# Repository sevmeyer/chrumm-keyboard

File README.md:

Chrumm keyboard
===============

Chrumm is an open-hardware ergonomic keyboard,
made of a 3D-printable body, a bendable PCB,
and custom firmware for the Raspberry Pi Pico.

This repository contains all relevant source files.
I share these files in the hope that they are useful, or
at least interesting to others. Keep in mind that this is
a free, do-it-yourself project. What you see is what you get.
Make sure to check the license.

Files
-----

- [Releases] - Download page for STL, 3MF, GBR, UF2 files
- [BUILD.md](BUILD.md) - Build advice
- [MATERIALS.md](MATERIALS.md) - Bill Of Materials
- [pcb/README.md](pcb/README.md) - PCB production details
- [body/README.md](body/README.md) - Body generator parameters
- [firmware/README.md](firmware/README.md) - Firmware overview and installation

[Releases]: https://github.com/sevmeyer/chrumm-keyboard/releases/

Features
--------

Chrumm features a column staggered layout with simple thumb clusters.
The right side has an additional column, to better approximate
the standard ANSI layout, and to provide dedicated arrow keys.
A central encoder allows for rotational input.

The body is a robust monoblock without visible screws. It has
integrated split, tent, and tilt angles, similar to commercial
ergonomic boards. The palm rests and the USB cable are firmly
attached, so that everything can be moved around without hassle.

The STL files are generated programmatically, with a pure
Python package that has no dependencies. They are optimized
for FFF 3D printing. Most parts are printed sideways, to
produce a smooth surface without the need of post-processing.
Custom supports minimize the print time and filament cost.

The body houses two reversible, bendable, interconnected PCBs.
They are powered by a Raspberry Pi Pico.

Layout
------

Credit
------

Chrumm would not exist without the shared knowledge of the
mechanical keyboard community.

I found inspiration on [Reddit], [KBD.news], [geekhack], and
learned a lot from the [PCB guides] by ai03 and Ruiqi Mao, the
[Keyboard posts] by Masterzen, and the [Matrix Help] by Dave Dribin.

The layout and body is influenced by projects like the [Ergodox],
[Dactyl], [Sofle], [Pteron], and everything from [Bastardkb].
I also used established open hardware repositories for reference,
including the [UHK60], [Skeletyl], [Sofle], [Corne], and [Torn].

[Reddit]: https://old.reddit.com/r/ErgoMechKeyboards+MechanicalKeyboards/
[KBD.news]: https://kbd.news/
[geekhack]: https://geekhack.org
[PCB guides]: https://wiki.ai03.com/books/pcb-design
[Keyboard posts]: https://www.masterzen.fr/tag/#mechanical-keyboards
[Matrix Help]: https://www.dribin.org/dave/keyboard/one_html/
[Ergodox]: https://www.ergodox.io/
[Dactyl]: https://github.com/adereth/dactyl-keyboard
[Sofle]: https://github.com/josefadamcik/SofleKeyboard
[Pteron]: https://github.com/FSund/pteron-keyboard
[Bastardkb]: https://bastardkb.com/
[UHK60]: https://github.com/UltimateHackingKeyboard/uhk60v1-electronics
[Skeletyl]: https://github.com/Bastardkb/Skeletyl-PCB-plate
[Corne]: https://github.com/foostan/crkbd
[Torn]: https://github.com/rtitmuss/torn

Gallery
-------

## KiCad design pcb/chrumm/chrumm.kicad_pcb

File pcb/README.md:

Chrumm PCB
==========

The PCB is made with [KiCad], version 7.

The PCB is reversible. It covers half of the keyboard,
and is flipped over for the other half. It is intended
to slightly bend between the pinky and ring finger,
therefore the board thickness should not exceed 0.8mm.

All connections are through-hole (or castelated), so
that they can be soldered with basic hobby equipment.
The switch pin holes are implemented as slots, to
provide a snug fit for the flat pins, and thus
minimize the required amount of solder.

[KiCad]: https://www.kicad.org/

Teardrops
---------

The teardrops are generated with a custom [KiCad plugin],
using the following settings:

    PTH arc radius: 250%
    SMD arc radius: 250%
    Via arc radius: 350%

[KiCad plugin]: https://github.com/sevmeyer/kicad-arc-teardrops

Production
----------

I ordered the prototypes from [PCBWay] (no affiliation).
Other manufacturers are available, check for example
[PCBShopper] or [Manufacturing Reports]. Here are some of
the relevant specifications, use them at your own discretion:

- Standard PCB (not flex)
- Single pieces (not panelized)
- Layers: 2
- Material: FR4 TG 150-160
- Thickness: 0.8mm (at most)
- Surface finish: HASL (lead free)
- Copper thickness: 1oz

[PCBWay]: https://pcbway.com/
[PCBShopper]: https://pcbshopper.com/
[Manufacturing Reports]: https://manufacturingreports.com/category/electronics/rigid-pcb-fabrication/

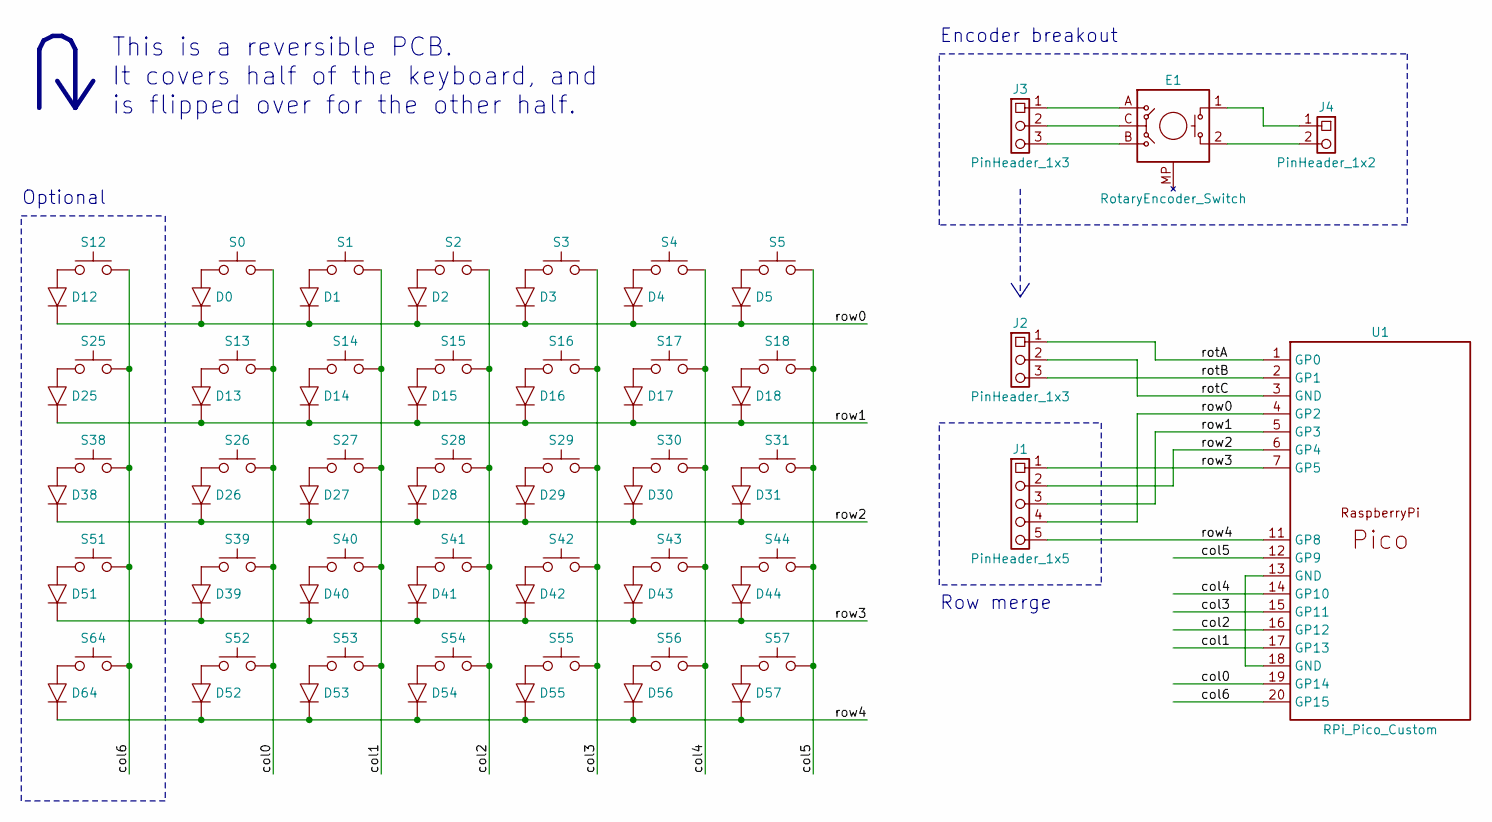
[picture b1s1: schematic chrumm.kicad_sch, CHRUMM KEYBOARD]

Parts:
D0, D1, D2, D3, D4, D5, D12, D13, D14, D15, D16, D17, D18, D25, D26, D27, D28, D29, D30, D31, D38, D39, D40, D41, D42, D43, D44, D51, D52, D53, D54, D55, D56, D57, D64: Diode
E1: RotaryEncoder_Switch
J1: PinHeader_1x5
J2, J3: PinHeader_1x3
J4: PinHeader_1x2
S0, S1, S2, S3, S4, S5, S12, S13, S14, S15, S16, S17, S18, S25, S26, S27, S28, S29, S30, S31, S38, S39, S40, S41, S42, S43, S44, S51, S52, S53, S54, S55, S56, S57, S64: Switch
U1: RPi_Pico_Custom

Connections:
/col0: S0.1, S13.1, S26.1, S39.1, S52.1, U1.19 (GP14)
/col1: S1.1, S14.1, S27.1, S40.1, S53.1, U1.17 (GP13)
/col2: S2.1, S15.1, S28.1, S41.1, S54.1, U1.16 (GP12)
/col3: S3.1, S16.1, S29.1, S42.1, S55.1, U1.15 (GP11)
/col4: S4.1, S17.1, S30.1, S43.1, S56.1, U1.14 (GP10)
/col5: S5.1, S18.1, S31.1, S44.1, S57.1, U1.12 (GP9)
/col6: S12.1, S25.1, S38.1, S51.1, S64.1, U1.20 (GP15)
/rotA: J2.1, U1.1 (GP0)
/rotB: J2.3, U1.2 (GP1)
/rotC: J2.2, U1.3 (GND)
/row0: D0.1 (K), D1.1 (K), D2.1 (K), D3.1 (K), D4.1 (K), D5.1 (K), D12.1 (K), J1.4, U1.4 (GP2)
/row1: D13.1 (K), D14.1 (K), D15.1 (K), D16.1 (K), D17.1 (K), D18.1 (K), D25.1 (K), J1.3, U1.5 (GP3)
/row2: D26.1 (K), D27.1 (K), D28.1 (K), D29.1 (K), D30.1 (K), D31.1 (K), D38.1 (K), J1.2, U1.6 (GP4)
/row3: D39.1 (K), D40.1 (K), D41.1 (K), D42.1 (K), D43.1 (K), D44.1 (K), D51.1 (K), J1.1, U1.7 (GP5)
/row4: D52.1 (K), D53.1 (K), D54.1 (K), D55.1 (K), D56.1 (K), D57.1 (K), D64.1 (K), J1.5, U1.11 (GP8)
unnamed: D0.2 (A), S0.2
unnamed: D1.2 (A), S1.2
unnamed: D2.2 (A), S2.2
unnamed: D3.2 (A), S3.2
unnamed: D4.2 (A), S4.2
unnamed: D5.2 (A), S5.2
unnamed: D12.2 (A), S12.2
unnamed: D13.2 (A), S13.2
unnamed: D14.2 (A), S14.2
unnamed: D15.2 (A), S15.2
unnamed: D16.2 (A), S16.2
unnamed: D17.2 (A), S17.2
unnamed: D18.2 (A), S18.2
unnamed: D25.2 (A), S25.2
unnamed: D26.2 (A), S26.2
unnamed: D27.2 (A), S27.2
unnamed: D28.2 (A), S28.2
unnamed: D29.2 (A), S29.2
unnamed: D30.2 (A), S30.2
unnamed: D31.2 (A), S31.2
unnamed: D38.2 (A), S38.2
unnamed: D39.2 (A), S39.2
unnamed: D40.2 (A), S40.2
unnamed: D41.2 (A), S41.2
unnamed: D42.2 (A), S42.2
unnamed: D43.2 (A), S43.2
unnamed: D44.2 (A), S44.2
unnamed: D51.2 (A), S51.2
unnamed: D52.2 (A), S52.2
unnamed: D53.2 (A), S53.2
unnamed: D54.2 (A), S54.2
unnamed: D55.2 (A), S55.2
unnamed: D56.2 (A), S56.2
unnamed: D57.2 (A), S57.2
unnamed: D64.2 (A), S64.2
unnamed: E1.1, J4.1
unnamed: E1.2, J4.2
unnamed: E1.A, J3.1
unnamed: E1.B, J3.3
unnamed: E1.C, J3.2
unnamed: U1.13 (GND), U1.18 (GND)

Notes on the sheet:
Encoder breakout
Optional
Row merge
This is a reversible PCB. It covers half of the keyboard, and is flipped over for the other half.

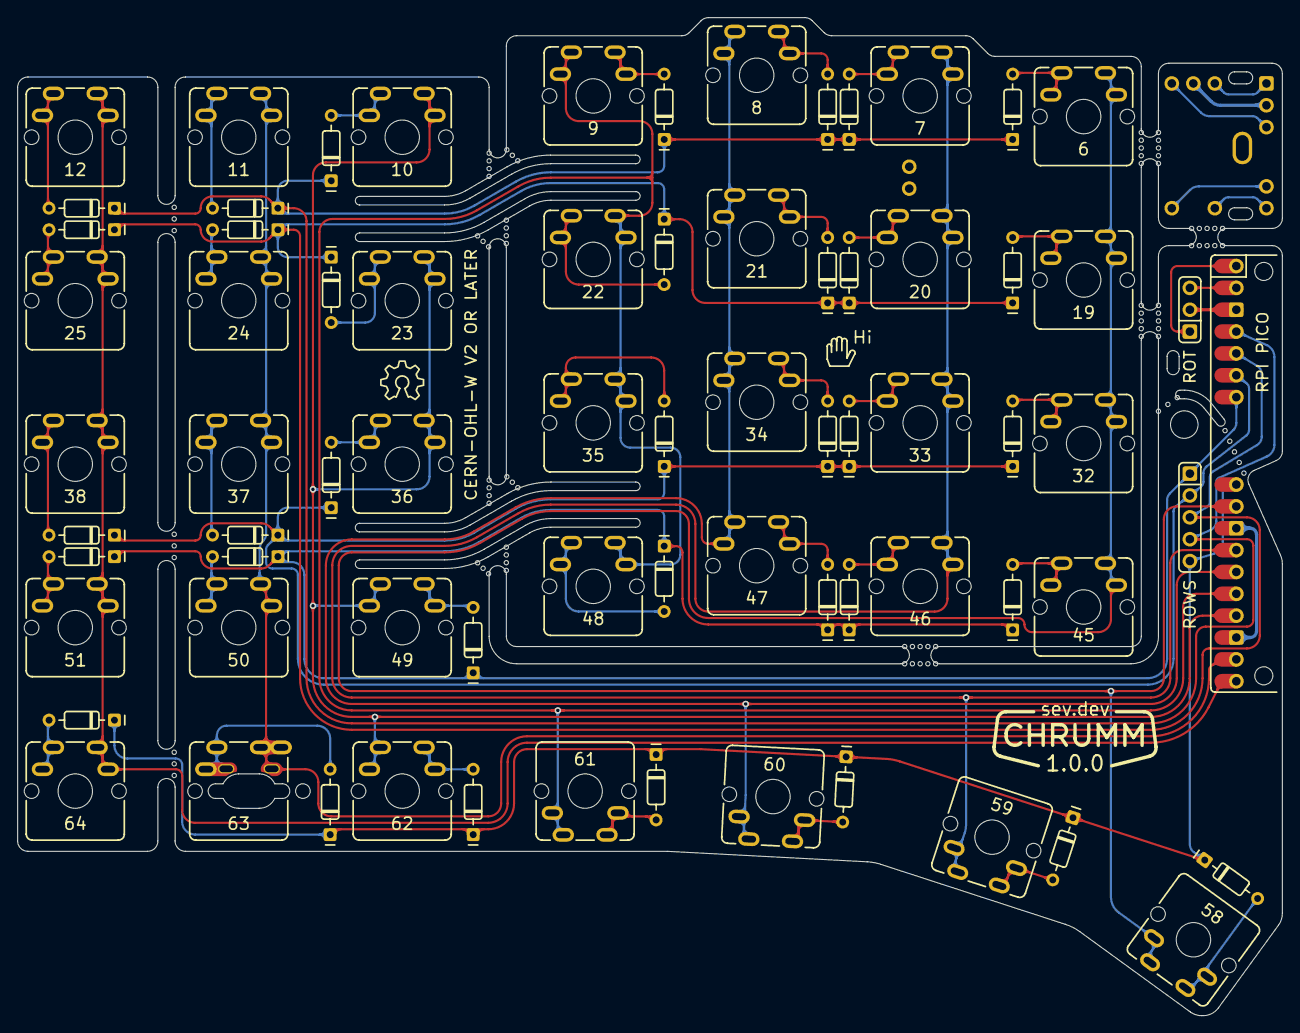
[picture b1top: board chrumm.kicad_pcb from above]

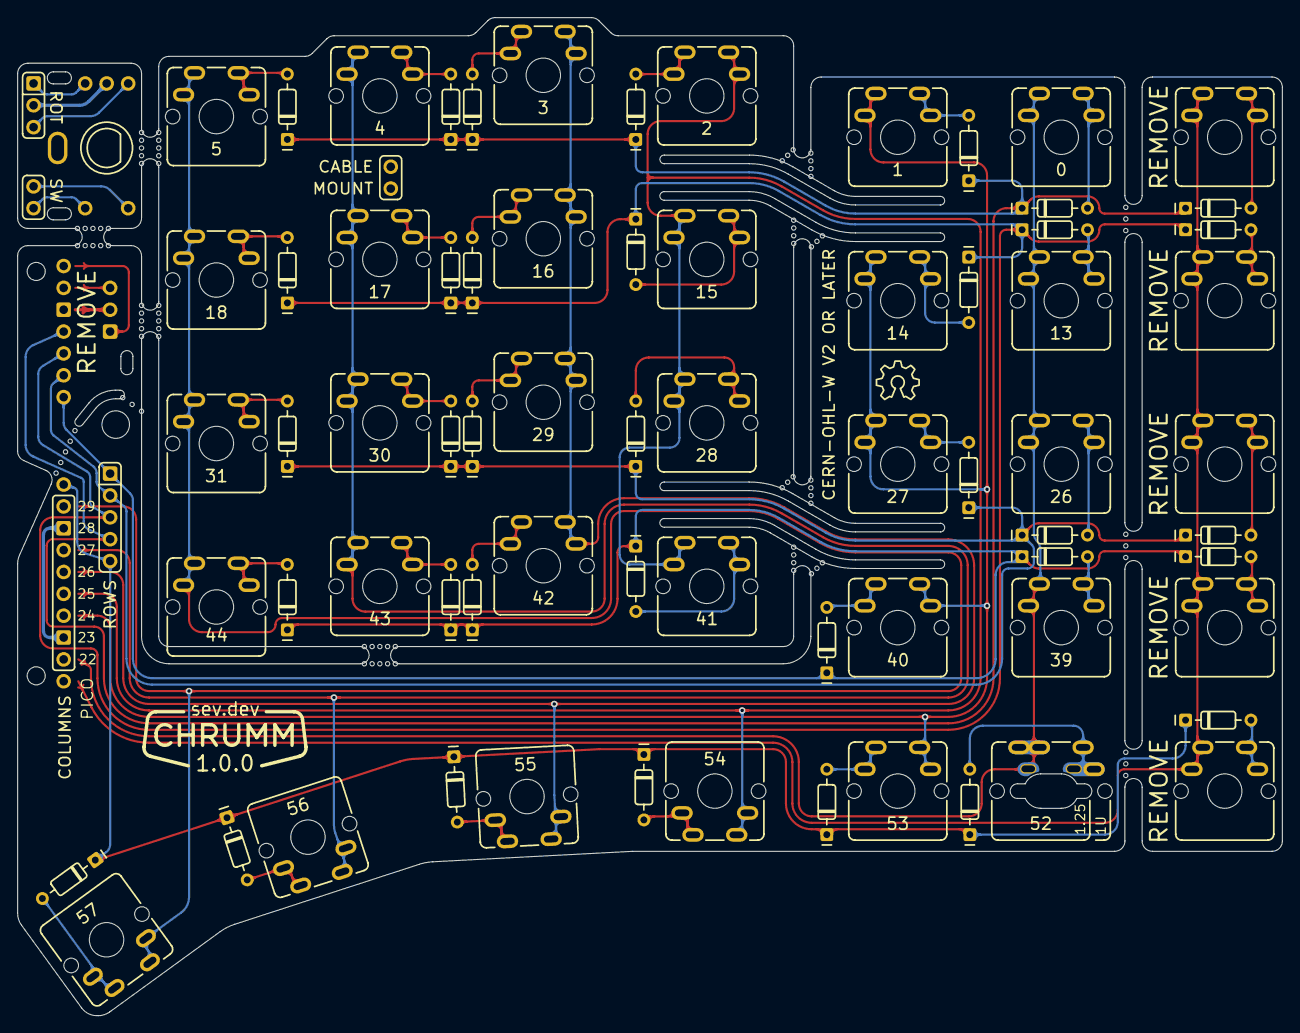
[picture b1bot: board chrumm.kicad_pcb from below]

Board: 2 copper layers, 147.0 x 116.0 mm, 76 parts (9 on the bottom side), 56 nets.

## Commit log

2020-07-03 Fix spelling
2020-08-13 Write each slice to separate file
2020-10-13 Update doc
2020-12-30 Update build log link
2022-09-17 Revise color in doc images
2023-10-04 Release version 1.0
2023-10-06 Add small clarifications to README
2023-10-08 Add keycap set name and diode advice to README
2023-10-09 Add layer count to PCB order details
2023-10-19 Add link to QMK config
2023-10-19 Add kBOOT keycode to trigger bootloader mode
2023-10-19 Remove cRWND and cFFWD from default layout
2023-11-07 Revise matrix comments in firmware
2023-11-07 Revise pin settle time and encoder keypress ticks
2023-11-07 Release firmware 1.0.1
2023-11-22 Revise matrix doc comments
2023-11-22 Use PID 1209:5E7C as registered on pid.codes
2023-12-03 Release firmware 1.0.2
2023-12-03 Revise Face triangulation for better performance
2023-12-03 Remove obsolete draft.json
2023-12-03 Revise body generator comments
2023-12-03 Release body generator 1.0.1
2024-03-07 Add body parameters for switches with side clips
2024-03-08 Fix CHANGELOG formatting
2024-03-14 assembly documentation
2024-03-17 Reorganize documentation files
2024-03-24 Expand build advice

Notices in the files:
pcb/chrumm/chrumm.kicad_pcb:
Licensed under CERN-OHL-W v2 or later
